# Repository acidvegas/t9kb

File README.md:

# T9KB

A tiny phone-style keypad for DIY projects that talks I2C. Plug it into an ESP32 *(or anything with Qwiic / I2C)* and you get the full key layout of an old desk phone handset: 3 soft keys, a 5-way d-pad, call / end / speaker / mute, and the 3x4 number pad.

There are virtually no good small modules on the market for basic I2C text input. The [M5Stack CardKB](https://docs.m5stack.com/en/unit/cardkb_1.1) is about the only one, and it is a tiny QWERTY board. Nothing like it exists for T9, so I made this one for T9 phone-style input on my own projects, starting with a DIY VoIP phone.

The layout follows the Grandstream WP826 handset. Keys are metal snap domes on gold pads, the same way real phones do it, and 3D printed PLA keycaps go on top. A single TI TCA8418 scans the keys, so the board has no firmware to flash. The text side *(multi-tap, T9, key repeat)* lives in an Arduino library on the host.

**Status:** v0.3 hardware is designed and ready to order, not built or tested yet. The Arduino library compiles and its logic is tested on a PC, not yet on real hardware. The keycaps and case are printed and fit.

<p align="center">
  
  &nbsp;
  
</p>
<p align="center">
  
  &nbsp;
  
</p>

The 3D model for case and keycap design is `hardware/t9kb.step`.

## Arduino library

The library is in `library/` *(Arduino, compiles for the ESP32 core)*. Install it by copying or symlinking `library/` into your Arduino `libraries` folder as `T9KB`.

```cpp
#include <Wire.h>
#include <T9KB.h>

T9KB keypad;

void setup() {
	Wire.begin();
	keypad.begin(); // or keypad.begin(Wire, INT_GPIO, RST_GPIO) with the INT / RST pads wired
}

void loop() {
	keypad.update();
	while (keypad.available()) {
		T9Event ev = keypad.read(); // ev.key, ev.type (press / release / long / repeat), ev.code (raw key number)
	}
	uint8_t c;
	while ((c = keypad.getChar())) {
		// typed text, CardKB style
	}
}
```

Text entry through `getChar()`:

| Key            | Tap in Abc / abc / ABC                            | Long press | 123 mode             |
| -------------- | ------------------------------------------------- | ---------- | -------------------- |
| 2 to 9         | Letters, then the digit *(abc2, def3, ... wxyz9)* | The digit  | Digit                |
| 1              | `1 . , ' ? ! " -`                                 | 1          | 1                    |
| 0              | Space                                             | 0          | 0, long press `+`    |
| `*`            | Symbols *(below)*                                 |            | `*`                  |
| `#`            | `#`                                               | Next mode  | `#`, long press mode |
| Right soft key | Backspace *(auto-repeats)*                        |            | Backspace            |
| Arrows         | CardKB arrow codes *(auto-repeat)*                |            | Arrow codes          |

The `*` symbols, in order: ``. , ' ? ! " - ( ) @ / : _ ; + % * = < > $ [ ] { } \ ~ ^ # | ` &``

- **Live preview:** each tap sends the letter right away, and the next tap on the same key sends a backspace plus the next letter. Show the text as it comes in and the screen previews every letter as you cycle. `pending()` is true while the last letter can still change, so you can underline it, and `tapSet()` returns the characters on that key *(`"abc2"` on 2)* so you can show the choices. It returns `nullptr` when nothing is pending. The letter is final after 800 ms or when another key is pressed.
- **Modes:** long press `#` cycles Abc, abc, ABC, 123. It starts in Abc, which capitalizes the first letter and any letter after `. `, `! ` or `? `. `setMode()` changes the mode from code.
- **Codes:** backspace `0x08`, left `0xB4`, up `0xB5`, down `0xB6`, right `0xB7`, the same values the M5Stack CardKB sends. `getChar()` returns 0 when nothing is waiting.
- **Events only:** OK, call, end, the left and middle soft keys, speaker and mute type nothing. Handle them from key events.
- **Events:** read them from the queue with `available()` / `read()`, or set a callback with `onKey()`. `isPressed()` works for every key, so combos like a soft key plus a digit work.
- **Timing:** `setTapTimeout()` *(800 ms)*, `setLongPress()` *(600 ms)* and `setRepeat()` *(500 ms delay, 80 ms rate)*.
- **Reading the keypad:** without INT the library polls every 10 ms over I2C. With INT wired it only reads when a key event is waiting.

| Example     | What it shows                                                        |
| ----------- | -------------------------------------------------------------------- |
| `Text`      | Line editor on the serial monitor with live preview and mode display |
| `Events`    | Prints every key event with its raw key number                       |
| `Dialer`    | 123 mode phone dialer using the `onKey()` callback, Call and End     |
| `DeepSleep` | ESP32 deep sleep, woken by a keypress on the INT wire                |

T9 word prediction is planned for later.

## Keys

One rigid PLA keycap per key, with no web or membrane. Each cap has a 0.75 mm flange underneath that the case plate holds in, and a small rigid plunger that rests on its dome. Only the dome pushes back, so every key takes the dome's own force and keeps its click. Caps are green with black digits, letters and icons in the top 0.2 mm. Each cap leaves 0.10 mm around it in its plate hole (`GROW`), and the 2.56 mm plate makes deep holes that guide the caps, so pressing a wide key near one end barely tips it.

<p align="center">
  
  &nbsp;
  
</p>

| File                         | What                                              |
| ---------------------------- | ------------------------------------------------- |
| `keys/t9kb_keys_caps.stl`    | All 24 caps, face down for printing               |
| `keys/t9kb_keys_legends.stl` | Black legends, lined up with the caps             |
| `keys/t9kb_keys.scad`        | OpenSCAD source with all dimensions as parameters |

Legends: digits and letters on the number keys, an envelope *(voicemail)* on 1, speaker, muted microphone, call and hang up icons on the side keys, a line on each soft key, and arrows on the d-pad. The center select key is blank. Every stroke and every gap is at least 0.36 mm, so a 0.4 mm nozzle prints them all.

Printing *(Bambu A1 mini, PLA, textured plate)*: `build/slice.py` slices every part with OrcaSlicer into ready-to-print `.gcode.3mf` files in `build/out/`:

| File                           | What                                                                                              |
| ------------------------------ | ------------------------------------------------------------------------------------------------- |
| `keys_2color_MANUAL.gcode.3mf` | Green caps, black legends: load black first, the printer pauses once in the first layer for green |
| `case_top.gcode.3mf`           | Case top only                                                                                     |
| `case.gcode.3mf`               | Case top and lid                                                                                  |

The caps print face down at 0.12 mm layers after a 0.2 mm first layer, so the legends are exactly the first layer. No supports.

| Part     | Size                                                                             |
| -------- | -------------------------------------------------------------------------------- |
| Caps     | Key sizes from the layout, 4.36 mm tall, stick out of the plate 1.0 mm           |
| Flange   | 0.75 mm wide, 0.8 mm thick, stops under the plate                                |
| Plungers | 1.2 mm on 5 mm domes, 1.0 mm on 4 mm domes *(Snaptron: at most 25% of the dome)* |
| Tip      | 0.40 mm above the board, resting on the dome                                     |
| D-pad    | 8 mm center key and 4 arrows, each with its own stop on the plate                |

`TIP` in `t9kb_keys.scad` is where the plunger meets the dome. ButtonWorx publishes no dome height; 5 mm round domes run 0.24 to 0.38 mm and the peel-and-stick film adds about 0.05 mm, so 0.40 leaves at most about 0.1 mm of free play. If the keys feel pre-pressed or don't click, raise it to 0.52. Keep `TOP - TIP` a multiple of the 0.12 mm layers after the 0.2 mm first one, then re-export and re-slice:

```
build/export.sh          # keycap and case STLs
python3 build/slice.py   # every .gcode.3mf
```

`slice.py` runs the OrcaSlicer 2.4.2 AppImage extracted to `~/.local/share/orca` *(`--appimage-extract`, needs `libwebkit2gtk-4.1-0` and `xvfb`)* with its stock Bambu A1 mini, Bambu PLA Basic and 0.12 mm Fine / 0.20 mm Standard profiles.

The keycap and case images in `preview/` are rendered from `build/preview.scad` *(`-D 'VIEW="keys"'`, `under`, `case`, `exploded` or `section`)*.

## Case

A 3D printed two-part case: a top shell with a hole for every key and a back lid. The keycaps and board drop into the top shell face down, then 4 M1.4 self-tapping screws go through the lid and the board's corner holes *(H1-H4)* into the face plate and clamp the stack together.

<p align="center">
  
  &nbsp;
  
</p>

| File                     | What                                               |
| ------------------------ | -------------------------------------------------- |
| `case/t9kb_case_top.stl` | Top shell, already flipped plate down for printing |
| `case/t9kb_case_lid.stl` | Back lid, floor down                               |
| `case/t9kb_case.scad`    | OpenSCAD source with all dimensions as parameters  |

| Part      | Size                                                                                                                                                              |
| --------- | ----------------------------------------------------------------------------------------------------------------------------------------------------------------- |
| Outside   | 52.6 x 72.6 x 8.8 mm                                                                                                                                              |
| Walls     | 2.0 mm                                                                                                                                                            |
| Top plate | 2.56 mm, deep key holes that keep the keys from tipping; keys stick out 1.0 mm                                                                                    |
| Spacer    | 1.6 mm under the plate, a pocket for every keycap flange; rests on a 1.0 mm rim at the board edge, the rest stays 0.3 mm off the board clear of the dome adhesive |
| Key holes | 0.25 mm around the key outline, 0.10 mm around each cap; a 1.4 mm ring and spokes split the d-pad                                                                 |
| Lid       | 1.2 mm floor, 1.2 mm skirt that holds the board against the spacer, a 3.4 mm boss under each board corner                                                         |
| Screws    | 4 x M1.4 x 8 mm self-tapping pan head *(PH00)*: 1.7 mm holes in the lid, 1.5 mm holes in the board, 1.2 mm pilots that stop 0.56 mm under the face                |
| Openings  | Qwiic slot on the top edge and a window in the lid for the jack, wire hole on the bottom edge for the J2 pads                                                     |
| Inside    | 1.8 mm under the board for the parts *(tallest is U1, 0.8 mm; the 2.96 mm Qwiic jack sits in the lid window, flush with the back)*                                |

Print both parts in PLA or PETG. 0.2 mm layers, 3 walls, no supports needed. The top shell prints plate down, so the face comes out flat.

Assembly:

1. Lay the top shell face down and drop every keycap into its hole from the inside, flange down.
2. Stick the domes on the board, then lay the board key face down onto the spacer.
3. Feed any J2 wires out through the bottom hole.
4. Set the lid in from the back and drive the 4 screws until snug. The first time they cut their own thread in the pilots, so don't overtighten.

## Specs

| Item        | Value                                                                               |
| ----------- | ----------------------------------------------------------------------------------- |
| Board size  | 48 x 68 mm, 1.6 mm thick, 2 layers, 2 mm corner radius                              |
| Keys        | 24 metal dome pads *(Snaptron patterns: 17 for 5 / 5.3 mm domes, 7 for 4 mm domes)* |
| Controller  | TI TCA8418 keypad scanner, no firmware                                              |
| I2C address | 0x34 *(fixed)*                                                                      |
| Power       | 3.3 V only *(1.65 to 3.6 V)*                                                        |
| Connector   | Qwiic / STEMMA QT *(JST SH 4-pin)*, top edge, parts side                            |
| Key face    | Flat: gold dome pads and legends only *(KiCad bottom layer)*                        |
| Parts side  | All parts *(8 total, KiCad top layer)*                                              |

## Key layout

All sizes in mm, measured on the key face. The key area is 43 x 63, centered on the board with a 2.5 border on every side.

| Keys         | Count | Size                          | Dome |
| ------------ | ----- | ----------------------------- | ---- |
| Soft keys    | 3     | 13 x 5                        | 4 mm |
| D-pad ring   |       | 18 circle                     |      |
| D-pad center | 1     | 10.5 circle                   | 5 mm |
| D-pad arrows | 4     | In the ring around the center | 4 mm |
| Side keys    | 4     | 10.5 x 7, two on each side    | 5 mm |
| Number keys  | 12    | 13 x 7                        | 5 mm |

| Gap                                    | Size |
| -------------------------------------- | ---- |
| Between soft keys, between number keys | 2    |
| Soft keys to d-pad                     | 3    |
| Soft keys to side keys                 | 3.5  |
| Between the 2 stacked side keys        | 3    |
| D-pad to number keys                   | 3    |
| Side keys to number keys               | 3.5  |

The outer edges of the soft keys, side keys and number keys all line up.

## Connections

Qwiic connector *(J1)*:

| Pin | Signal |
| --- | ------ |
| 1   | GND    |
| 2   | 3.3V   |
| 3   | SDA    |
| 4   | SCL    |

Breakout pads on the bottom edge of the parts side *(J2, 2.54 mm pitch, solder wires or an SMD header)*:

| Pad | Signal | Notes                                                         |
| --- | ------ | ------------------------------------------------------------- |
| 1   | GND    |                                                               |
| 2   | 3V3    |                                                               |
| 3   | SDA    |                                                               |
| 4   | SCL    |                                                               |
| 5   | INT    | Goes low when a key event is waiting *(10k pull-up on board)* |
| 6   | RST    | Pull low to reset the TCA8418 *(10k pull-up on board)*        |

Qwiic has no spare wire for INT. Over Qwiic alone the host polls the keypad; solder a wire from J2's INT pad to a GPIO for interrupt-driven reads and wake-on-keypress.

The board has 4.7k I2C pull-ups through the 3-pad solder jumper JP1. It comes bridged. If you chain it with other boards that already have pull-ups, cut both copper bars on JP1.

## Key map

The TCA8418 reports a key number from 1 to 80 *(`row * 10 + column + 1`)*. Bit 7 of the event byte is 1 for press, 0 for release.

| Key         | Row | Col | Key number |
| ----------- | --- | --- | ---------- |
| 1           | 0   | 0   | 1          |
| 2           | 0   | 1   | 2          |
| 3           | 0   | 2   | 3          |
| Soft left   | 0   | 3   | 4          |
| Soft middle | 0   | 4   | 5          |
| Soft right  | 0   | 5   | 6          |
| 4           | 1   | 0   | 11         |
| 5           | 1   | 1   | 12         |
| 6           | 1   | 2   | 13         |
| Speaker     | 1   | 3   | 14         |
| Up          | 1   | 4   | 15         |
| Mute        | 1   | 5   | 16         |
| 7           | 2   | 0   | 21         |
| 8           | 2   | 1   | 22         |
| 9           | 2   | 2   | 23         |
| Left        | 2   | 3   | 24         |
| OK          | 2   | 4   | 25         |
| Right       | 2   | 5   | 26         |
| *           | 3   | 0   | 31         |
| 0           | 3   | 1   | 32         |
| #           | 3   | 2   | 33         |
| Call        | 3   | 3   | 34         |
| Down        | 3   | 4   | 35         |
| End         | 3   | 5   | 36         |

Minimum setup over I2C:

| Register | Name     | Write | Why                               |
| -------- | -------- | ----- | --------------------------------- |
| 0x1D     | KP_GPIO1 | 0x0F  | Rows 0 to 3 are keypad rows       |
| 0x1E     | KP_GPIO2 | 0x3F  | Columns 0 to 5 are keypad columns |
| 0x01     | CFG      | 0x01  | Interrupt on key events           |

Then read `KEY_LCK_EC` *(0x03)* for the event count, read `KEY_EVENT_A` *(0x04)* once per event, and write 0x01 to `INT_STAT` *(0x02)* to clear the interrupt.

The board has no diodes, so single keys and 2-key combos are reliable. Pressing 3 keys that form an L in the matrix can show a fake 4th key.

## Parts

Assembled by JLCPCB *(all on the parts side)*:

| Ref    | Part                        | Package         | LCSC    | JLC type |
| ------ | --------------------------- | --------------- | ------- | -------- |
| U1     | TCA8418RTWR                 | WQFN-24 4x4 mm  | C138713 | Extended |
| J1     | JST SM04B-SRSS-TB *(Qwiic)* | SMD right angle | C160404 | Extended |
| C1     | 100 nF                      | 0603            | C14663  | Basic    |
| C2     | 10 uF                       | 0603            | C19702  | Basic    |
| R1, R2 | 4.7k *(I2C pull-ups)*       | 0603            | C23162  | Basic    |
| R3, R4 | 10k *(RST, INT pull-ups)*   | 0603            | C25804  | Basic    |

Bought separately and added by hand:

| Qty | Part                                         | Where    | Notes                      |
| --- | -------------------------------------------- | -------- | -------------------------- |
| 20  | 5 to 5.3 mm metal domes *(see Dome sources)* | Varies   | 17 needed, rest are spares |
| 10  | 4 mm metal domes *(see Dome sources)*        | Varies   | 7 needed, rest are spares  |
| 1   | Kapton *(polyimide)* tape                    | Anywhere | Only for loose domes       |

## Dome sources

The pads follow Snaptron's published single-sided contact patterns: 17 pads for 5 / 5.3 mm domes and 7 pads for 4 mm domes *(soft keys and d-pad arrows)*. Prices and stock were checked on 2026-10-07.

From [ButtonWorx](https://buttonworx.com) *(Maine, US, $4 minimum order, no force listed)*:

| Pads | Part                                                                                                                    | Price      | Mounting                     |
| ---- | ----------------------------------------------------------------------------------------------------------------------- | ---------- | ---------------------------- |
| 5 mm | [Snap Dome Chopped Circle 5.2mm Peel & Stick](https://buttonworx.com/metal-domes/291-snap-dome-cut-circle-5-2x3-8.html) | $0.50 each | Built-in 7 mm square sticker |
| 4 mm | [Snap Dome Round 4mm Dimple](https://buttonworx.com/metal-domes/284-snap-dome-round-4mmD.html), loose                   | $0.40 each | Loose: tape it down          |

The adhesive squares around neighboring d-pad domes may overlap; trim them if they do. A 4.5 mm dome does not fit the 4 mm pads.

## Ordering from JLCPCB

Upload `hardware/fab/t9kb_gerbers.zip` and use these settings:

| Setting        | Value                                               |
| -------------- | --------------------------------------------------- |
| Layers         | 2                                                   |
| Dimensions     | 48 x 68 mm *(auto-detected)*                        |
| Material       | FR-4                                                |
| PCB thickness  | 1.6 mm *(Economic PCBA only offers ENIG at 1.6 mm)* |
| Surface finish | ENIG *(required, the dome contacts need gold)*      |
| Gold thickness | 2U" *(1U" also works)*                              |
| PCB assembly   | Yes, Economic                                       |
| Assembly side  | Top side                                            |
| BOM / CPL      | `hardware/fab/BOM.csv` and `hardware/fab/CPL.csv`   |

On the placement preview page, check these before paying:

- **U1:** the dot on the chip lines up with the pin 1 triangle printed on the board.
- **J1:** the connector opening faces the top edge of the board.

If either is turned wrong, rotate it right there in the preview. Resistors and capacitors do not care.

## Assembly

1. Clean the key face with isopropyl alcohol.
2. Place a dome on each gold pad, centered on the round contact *(not on the small hole, which is off-center on purpose)*. The small pads *(soft keys and d-pad arrows)* take 4 mm domes, the rest take 5 mm domes. Four-leg domes go with a leg on each of the 4 cut corners of the gold frame.
3. Tape over the domes with Kapton tape, or use peel-and-stick domes. Air vents through the small hole in each center pad, so the tape can cover the domes fully.
4. Test by pressing each dome with a finger while reading key events.

A dome that sits crooked can be peeled off and placed again. Nothing on the key face is soldered.

## Rebuilding the board

The board is generated by script *(KiCad 9)*. There is no schematic; the netlist lives in `gen_pcb.py`.

```
cd hardware
./autoroute.sh    # place parts, autoroute with freerouting, pour ground, run DRC
python3 fab.py    # gerbers, drill files, BOM, CPL
```

`autoroute.sh` expects `freerouting.jar` in `tools/`. Download it from the [freerouting v2.0.1 release](https://github.com/freerouting/freerouting/releases/tag/v2.0.1) *(needs Java 21)*.

## References

- `ref/tca8418.pdf`: [TI TCA8418 datasheet](https://www.ti.com/lit/ds/symlink/tca8418.pdf)
- `ref/snaptron_guide.pdf`: Snaptron metal dome design guide *(contact pad patterns, plating, venting)*

## Notes

- The TCA8418 exposed pad is tied to ground, as TI recommends *(ground or floating, never power)*.
- Dome pads follow Snaptron's single-sided contact patterns for 5 / 5.3 mm and 4 mm domes, with the off-center via-in-pad option for 2-layer boards. There is no solder mask inside the pad area, per Snaptron.
- U1 uses TI's own land pattern and stencil for the RTW0024B package *(TCA8418 datasheet)*.
- The key face is the KiCad bottom layer so JLC assembles the top side.
- LEDs and backlight were removed for this revision. They may come back later.

---

###### Mirrors: [SuperNETs](https://git.supernets.org/acidvegas/) • [GitHub](https://github.com/acidvegas/) • [GitLab](https://gitlab.com/acidvegas/) • [Codeberg](https://codeberg.org/acidvegas/)

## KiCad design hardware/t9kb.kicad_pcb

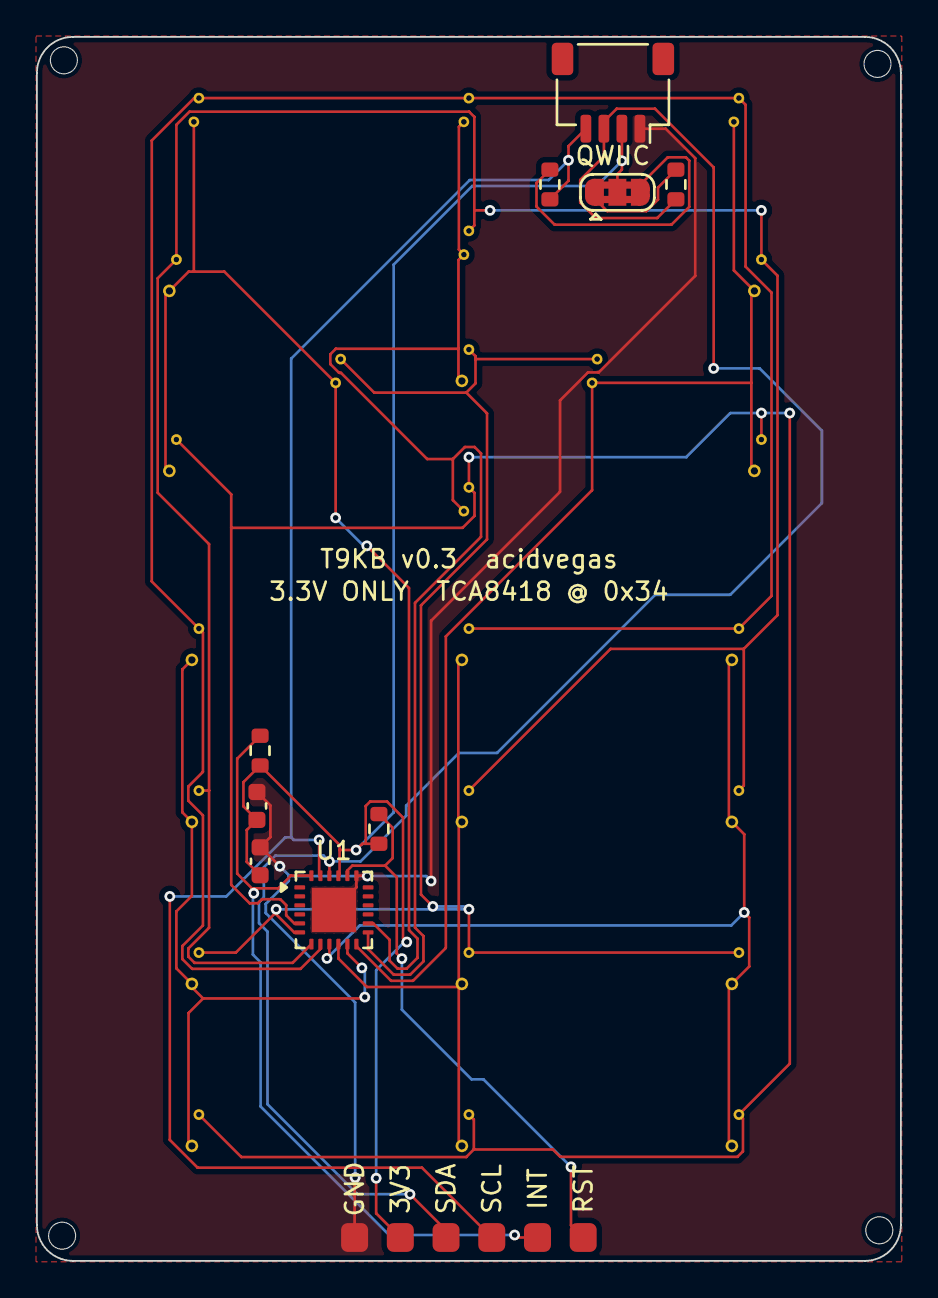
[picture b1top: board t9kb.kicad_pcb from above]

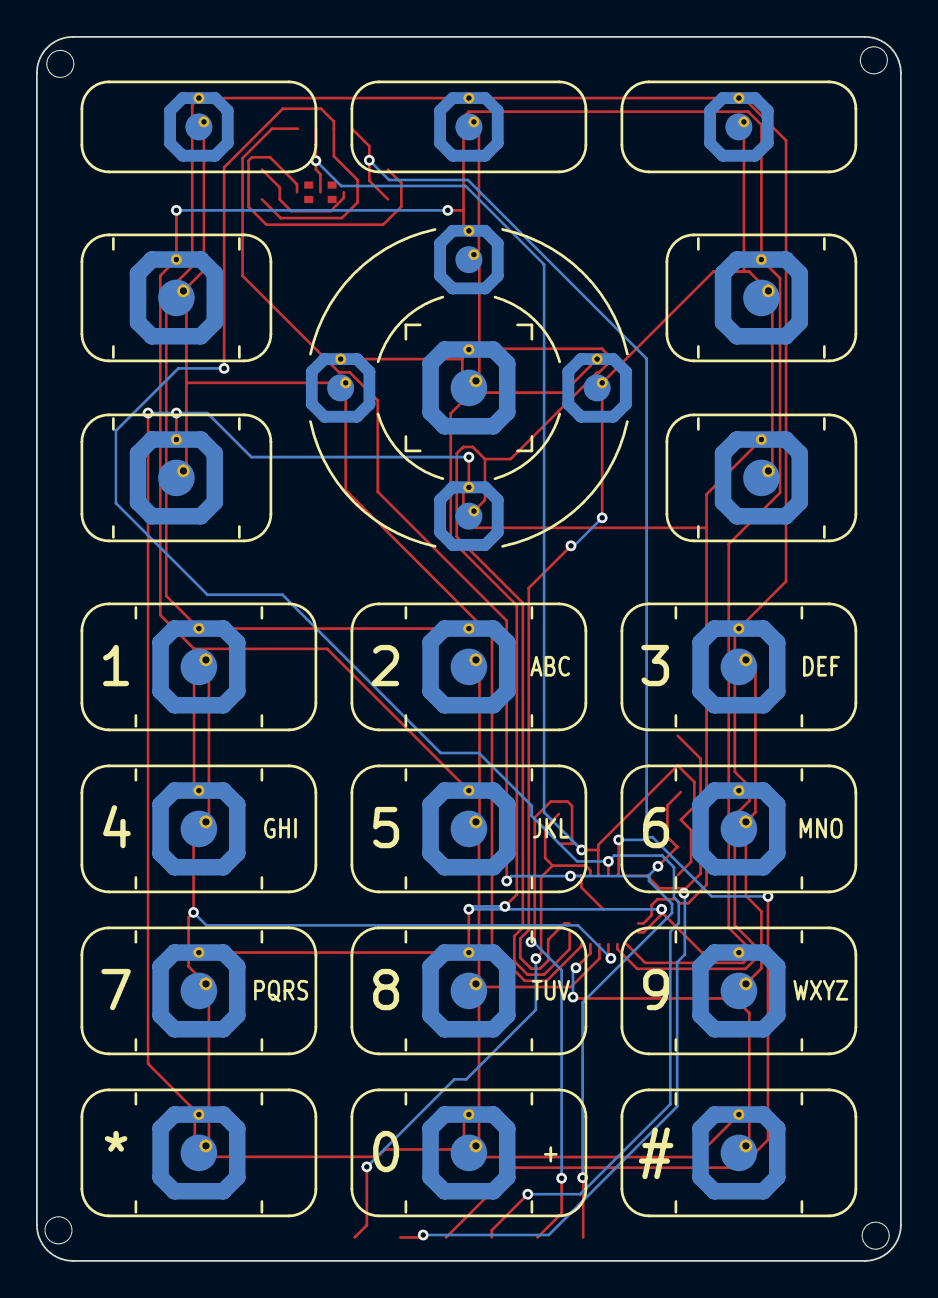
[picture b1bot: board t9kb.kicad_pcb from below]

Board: 2 copper layers, 48.0 x 68.0 mm, 38 parts (24 on the bottom side), 18 nets.

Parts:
C1: 100nF; C_0603_1608Metric
C2: 10uF; C_0603_1608Metric
H1, H2, H3, H4: M1.4; MountingHole_1.5mm_M1.4
J1: Qwiic; JST_SH_SM04B-SRSS-TB_1x04-1MP_P1.00mm_Horizontal
J2: Breakout; Pads_1x06_P2.54mm_SMD
JP1: I2C_PU; SolderJumper-3_P1.3mm_Bridged2Bar123_RoundedPad1.0x1.5mm
R1, R2: 4.7k; R_0603_1608Metric
R3, R4: 10k; R_0603_1608Metric
SW1: SOFT_L; MetalDome_4mm
SW2: SOFT_M; MetalDome_4mm
SW3: SOFT_R; MetalDome_4mm
SW4: SPK; MetalDome_5mm
SW5: UP; MetalDome_4mm
SW6: CONTACT; MetalDome_5mm
SW7: LEFT; MetalDome_4mm
SW8: OK; MetalDome_5mm
SW9: RIGHT; MetalDome_4mm
SW10: CALL; MetalDome_5mm
SW11: DOWN; MetalDome_4mm
SW12: END; MetalDome_5mm
SW13: K1; MetalDome_5mm
SW14: K2; MetalDome_5mm
SW15: K3; MetalDome_5mm
SW16: K4; MetalDome_5mm
SW17: K5; MetalDome_5mm
SW18: K6; MetalDome_5mm
SW19: K7; MetalDome_5mm
SW20: K8; MetalDome_5mm
SW21: K9; MetalDome_5mm
SW22: KSTAR; MetalDome_5mm
SW23: K0; MetalDome_5mm
SW24: KHASH; MetalDome_5mm
U1: TCA8418RTWR; WQFN-24-1EP_4x4mm_P0.5mm_EP2.45mm_TI_RTW0024B

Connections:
+3V3: C1.1, C2.1, J1.2, J2.2, JP1.2, R3.1, R4.1, U1.21
COL0: SW13.1, SW16.1, SW19.1, SW22.1, U1.9
COL1: SW14.1, SW17.1, SW20.1, SW23.1, U1.10
COL2: SW15.1, SW18.1, SW21.1, SW24.1, U1.11
COL3: SW1.1, SW4.1, SW7.1, SW10.1, U1.12
COL4: SW2.1, SW5.1, SW8.1, SW11.1, U1.13
COL5: SW3.1, SW6.1, SW9.1, SW12.1, U1.14
GND: C1.2, C2.2, J1.1, J2.1, U1.19, U1.25
INT: J2.5, R4.2, U1.24
PU_SCL: JP1.3, R2.2
PU_SDA: JP1.1, R1.2
ROW0: SW1.2, SW2.2, SW3.2, SW13.2, SW14.2, SW15.2, U1.8
ROW1: SW4.2, SW5.2, SW6.2, SW16.2, SW17.2, SW18.2, U1.7
ROW2: SW7.2, SW8.2, SW9.2, SW19.2, SW20.2, SW21.2, U1.6
ROW3: SW10.2, SW11.2, SW12.2, SW22.2, SW23.2, SW24.2, U1.5
RST: J2.6, R3.2, U1.20
SCL: J1.4, J2.4, R2.1, U1.23
SDA: J1.3, J2.3, R1.1, U1.22
